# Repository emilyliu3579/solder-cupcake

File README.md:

# solder-cupcake
I made a cupcake design for the PCB that has lights for sprinkles and a button that starts the motor to vibrate.

Materials used:
- 4 LEDs
- 5 resistors
- 1 Battery Holder
- 1 Push Button
- 1 DC Motor

Screenshots

Made by @emilyliu3579 on Slack

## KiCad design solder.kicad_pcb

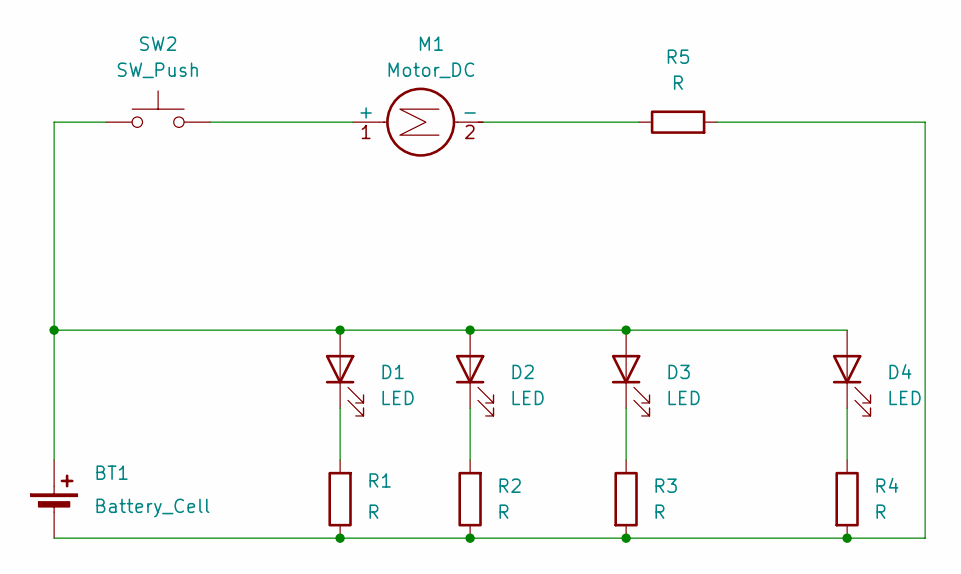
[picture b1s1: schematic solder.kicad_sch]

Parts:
BT1: Battery_Cell; BatteryHolder_MPD_BC2003_1x2032
D1, D2, D3, D4: LED; LED_D5.0mm
M1: Motor_DC; PinHeader_1x02_P2.54mm_Vertical
R1, R2, R3, R4, R5: R; R_Axial_DIN0207_L6.3mm_D2.5mm_P7.62mm_Horizontal
SW2: SW_Push; SW_PUSH_6mm

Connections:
unnamed: BT1.1 (+), D1.2 (A), D2.2 (A), D3.2 (A), D4.2 (A), SW2.1
unnamed: BT1.2 (-), R1.1, R2.1, R3.2, R4.2, R5.2
unnamed: D1.1 (K), R1.2
unnamed: D2.1 (K), R2.2
unnamed: D3.1 (K), R3.1
unnamed: D4.1 (K), R4.1
unnamed: M1.1 (+), SW2.2
unnamed: M1.2 (-), R5.1

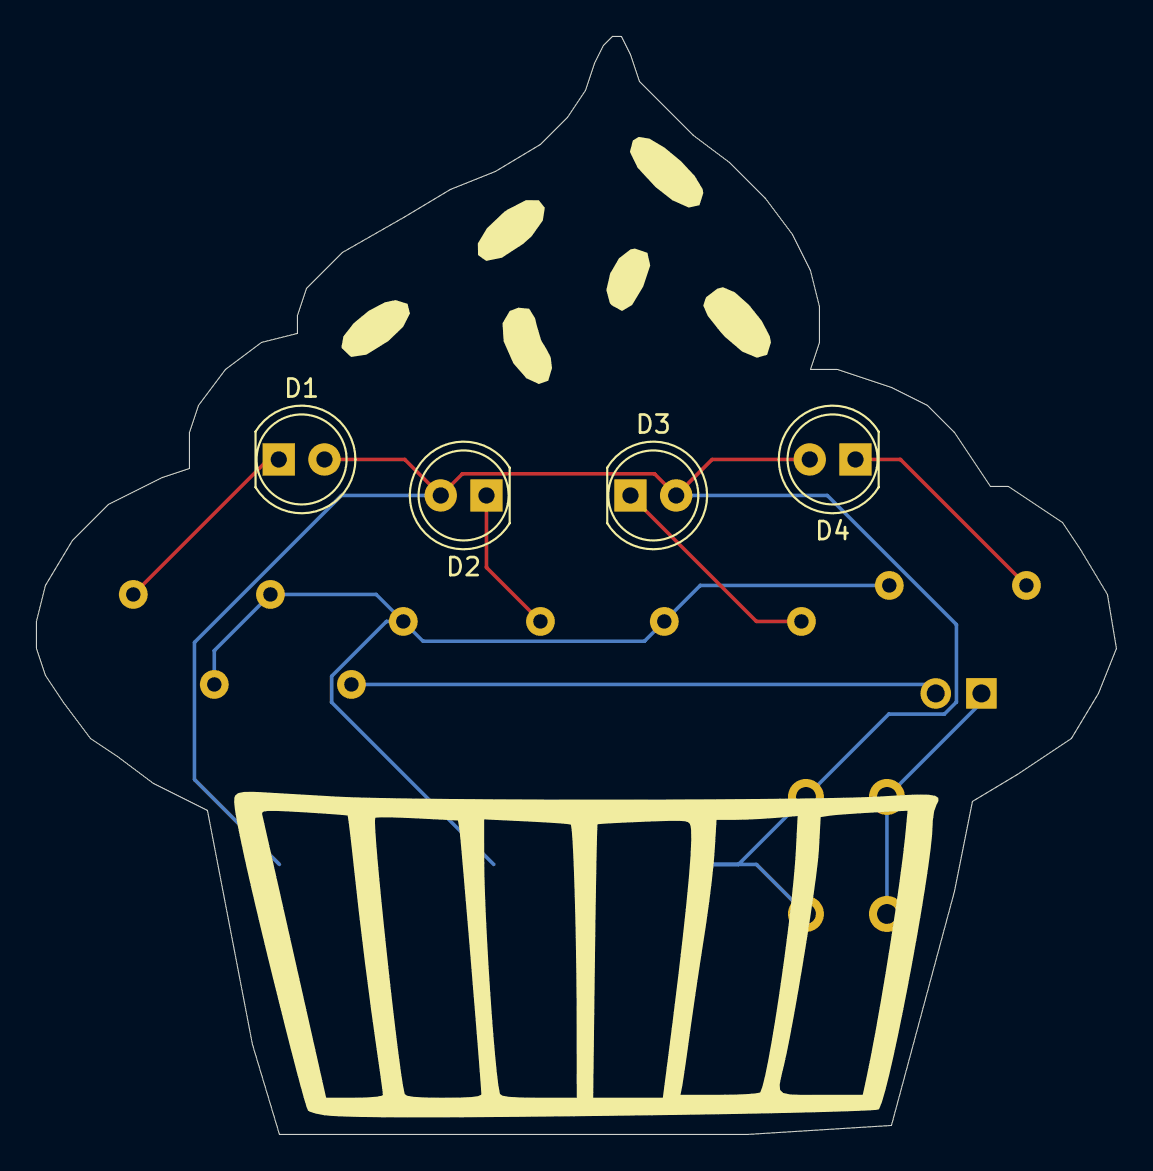
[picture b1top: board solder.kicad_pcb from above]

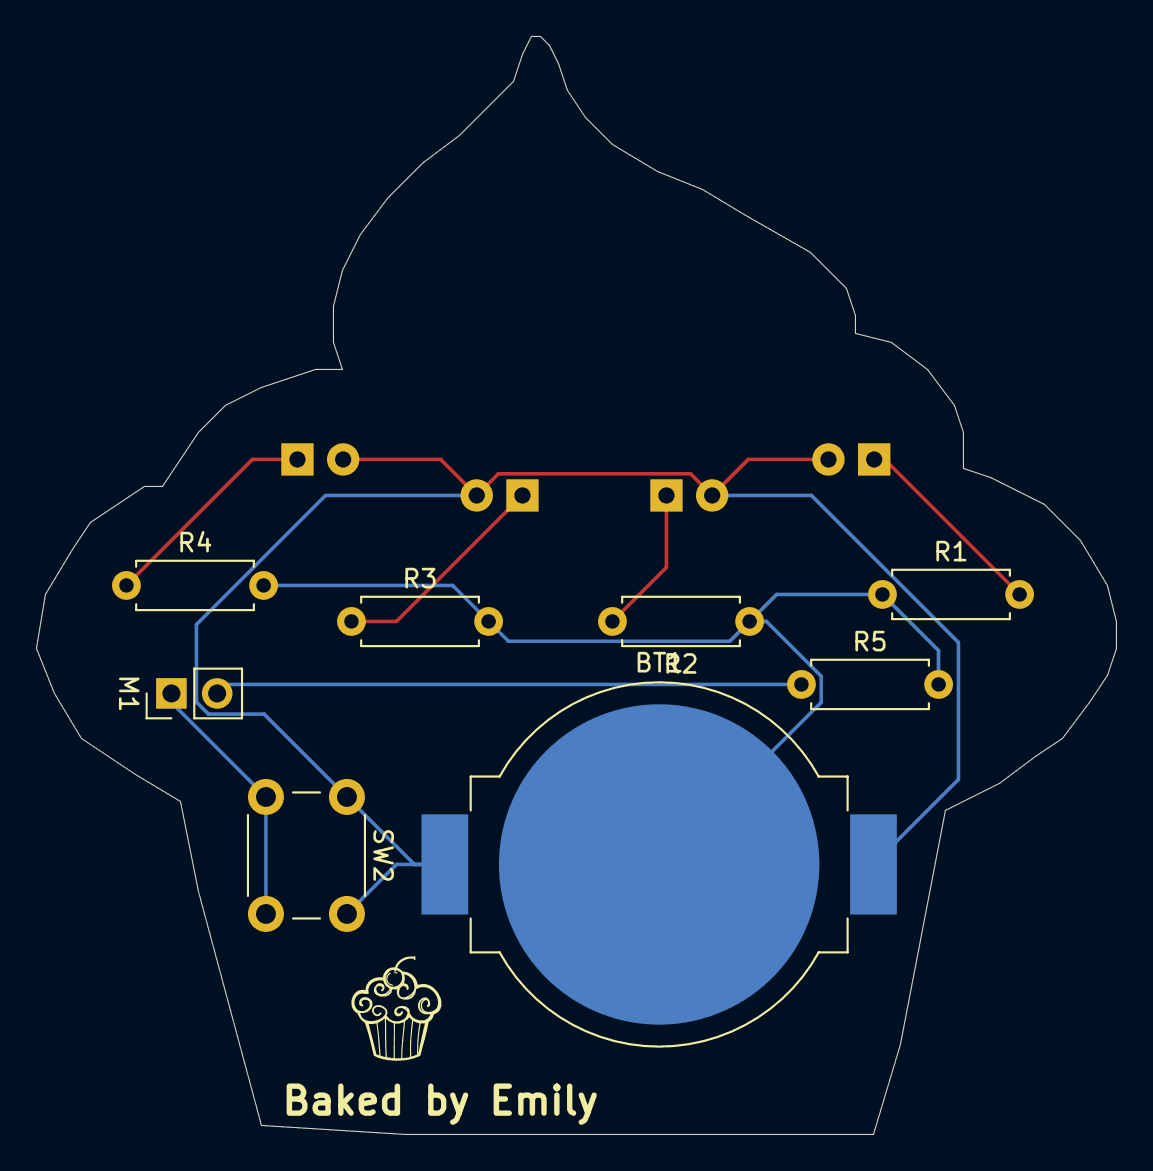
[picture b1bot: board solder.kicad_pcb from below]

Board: 2 copper layers, 60.0 x 61.0 mm, 12 parts (8 on the bottom side), 8 nets.

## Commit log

2025-06-24 updated silkscreens
2025-06-24 updated silkscreen
